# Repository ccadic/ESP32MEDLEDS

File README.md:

# ESP32MEDLEDS
ESP32 Medical LED driving board POC

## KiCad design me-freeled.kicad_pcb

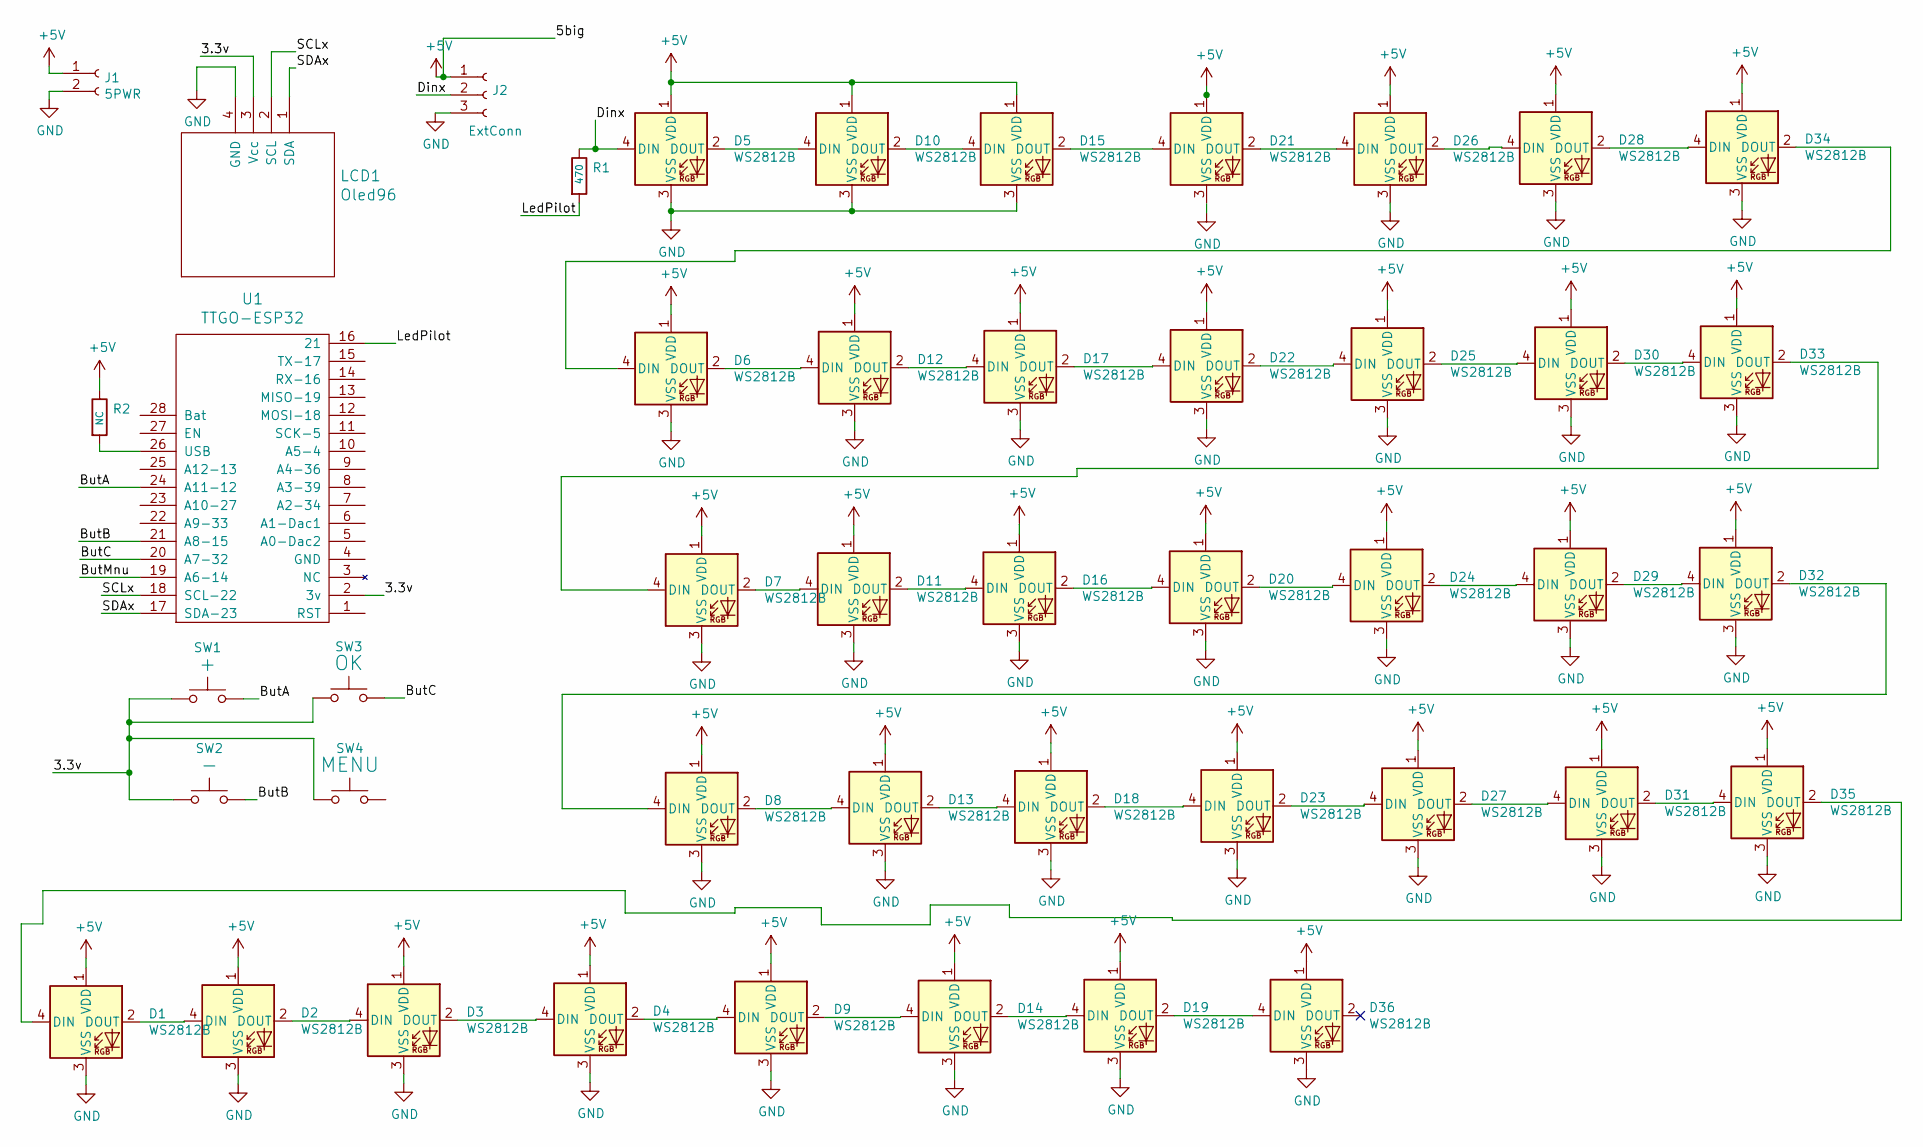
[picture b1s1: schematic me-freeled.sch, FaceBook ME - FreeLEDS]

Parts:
D1, D2, D3, D4, D5, D6, D7, D8, D9, D10, D11, D12, D13, D14, D15, D16, D17, D18, D19, D20, D21, D22, D23, D24, D25, D26, D27, D28, D29, D30, D31, D32, D33, D34, D35, D36: WS2812B
J1: 5PWR; BARREL_JACK
J2: ExtConn; Socket_Strip_Straight_1x03_Pitch2.54mm
LCD1: Oled96
R1: 470; R_1206_HandSoldering
R2: NC; R_1206_HandSoldering
SW1: +; SW_SPST_B3S-1000
SW2: -; SW_SPST_B3S-1000
SW3: OK; SW_SPST_B3S-1000
SW4: MENU; SW_SPST_B3S-1000
U1: TTGO-ESP32

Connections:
+5V: D1.1 (VDD), D2.1 (VDD), D3.1 (VDD), D4.1 (VDD), D5.1 (VDD), D6.1 (VDD), D7.1 (VDD), D8.1 (VDD), D9.1 (VDD), D10.1 (VDD), D11.1 (VDD), D12.1 (VDD), D13.1 (VDD), D14.1 (VDD), D15.1 (VDD), D16.1 (VDD), D17.1 (VDD), D18.1 (VDD), D19.1 (VDD), D20.1 (VDD), D21.1 (VDD), D22.1 (VDD), D23.1 (VDD), D24.1 (VDD), D25.1 (VDD), D26.1 (VDD), D27.1 (VDD), D28.1 (VDD), D29.1 (VDD), D30.1 (VDD), D31.1 (VDD), D32.1 (VDD), D33.1 (VDD), D34.1 (VDD), D35.1 (VDD), D36.1 (VDD), J1.1, J2.1, R2.1
/3.3v: LCD1.3 (Vcc), SW1.1, SW2.1, SW3.1, SW4.1, U1.2 (3v)
/ButA: SW1.2, U1.24 (A11-12)
/ButB: SW2.2, U1.21 (A8-15)
/ButC: SW3.2, U1.20 (A7-32)
/Dinx: D5.4 (DIN), J2.2, R1.1
/LedPilot: R1.2, U1.16 (21)
/SCLx: LCD1.2 (SCL), U1.18 (SCL-22)
/SDAx: LCD1.1 (SDA), U1.17 (SDA-23)
GND: D1.3 (VSS), D2.3 (VSS), D3.3 (VSS), D4.3 (VSS), D5.3 (VSS), D6.3 (VSS), D7.3 (VSS), D8.3 (VSS), D9.3 (VSS), D10.3 (VSS), D11.3 (VSS), D12.3 (VSS), D13.3 (VSS), D14.3 (VSS), D15.3 (VSS), D16.3 (VSS), D17.3 (VSS), D18.3 (VSS), D19.3 (VSS), D20.3 (VSS), D22.3 (VSS), D23.3 (VSS), D24.3 (VSS), D25.3 (VSS), D26.3 (VSS), D27.3 (VSS), D28.3 (VSS), D29.3 (VSS), D30.3 (VSS), D31.3 (VSS), D32.3 (VSS), D33.3 (VSS), D34.3 (VSS), D35.3 (VSS), D36.3 (VSS), J1.2, J2.3, LCD1.4 (GND)
unnamed: D1.2 (DOUT), D2.4 (DIN)
unnamed: D1.4 (DIN), D35.2 (DOUT)
unnamed: D2.2 (DOUT), D3.4 (DIN)
unnamed: D3.2 (DOUT), D4.4 (DIN)
unnamed: D4.2 (DOUT), D9.4 (DIN)
unnamed: D10.2 (DOUT), D15.4 (DIN)
unnamed: D5.2 (DOUT), D10.4 (DIN)
unnamed: D11.2 (DOUT), D16.4 (DIN)
unnamed: D7.2 (DOUT), D11.4 (DIN)
unnamed: D12.2 (DOUT), D17.4 (DIN)
unnamed: D6.2 (DOUT), D12.4 (DIN)
unnamed: D13.2 (DOUT), D18.4 (DIN)
unnamed: D8.2 (DOUT), D13.4 (DIN)
unnamed: D14.2 (DOUT), D19.4 (DIN)
unnamed: D9.2 (DOUT), D14.4 (DIN)
unnamed: D15.2 (DOUT), D21.4 (DIN)
unnamed: D16.2 (DOUT), D20.4 (DIN)
unnamed: D17.2 (DOUT), D22.4 (DIN)
unnamed: D18.2 (DOUT), D23.4 (DIN)
unnamed: D19.2 (DOUT), D36.4 (DIN)
unnamed: D20.2 (DOUT), D24.4 (DIN)
unnamed: D21.2 (DOUT), D26.4 (DIN)
unnamed: D22.2 (DOUT), D25.4 (DIN)
unnamed: D23.2 (DOUT), D27.4 (DIN)
unnamed: D24.2 (DOUT), D29.4 (DIN)
unnamed: D25.2 (DOUT), D30.4 (DIN)
unnamed: D26.2 (DOUT), D28.4 (DIN)
unnamed: D27.2 (DOUT), D31.4 (DIN)
unnamed: D28.2 (DOUT), D34.4 (DIN)
unnamed: D29.2 (DOUT), D32.4 (DIN)
unnamed: D30.2 (DOUT), D33.4 (DIN)
unnamed: D31.2 (DOUT), D35.4 (DIN)
unnamed: D8.4 (DIN), D32.2 (DOUT)
unnamed: D7.4 (DIN), D33.2 (DOUT)
unnamed: D6.4 (DIN), D34.2 (DOUT)
unnamed: R2.2, U1.26 (USB)

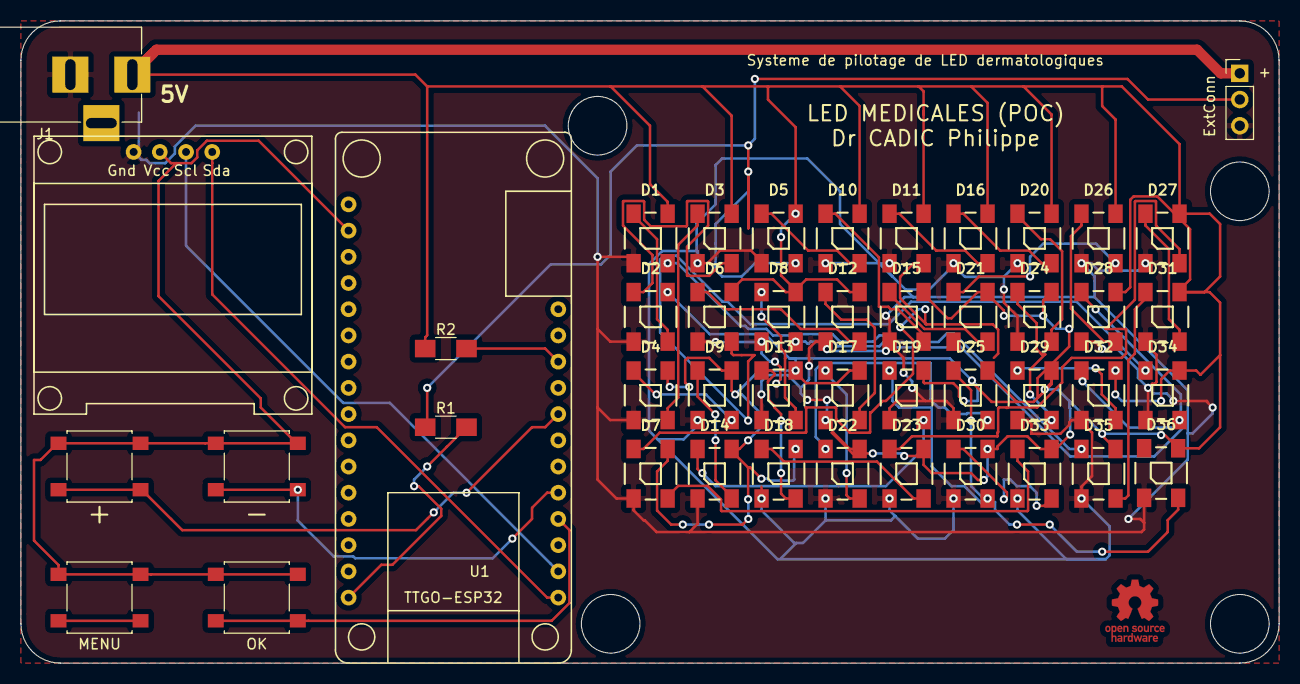
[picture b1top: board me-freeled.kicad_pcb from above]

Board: 2 copper layers, 121.9 x 62.2 mm, 46 parts (0 on the bottom side), 46 nets.
